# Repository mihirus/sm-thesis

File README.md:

```bash
├── cad
│   ├── cores
│   │   ├── etd44_core.SLDPRT
│   │   ├── etd49_core.SLDPRT
│   │   ├── etd54_core.SLDPRT
│   │   └── etd59_core.SLDPRT
│   ├── etd59_bobbin_integrated_secondary.SLDPRT
│   ├── etd59_shunt_AB.SLDPRT
│   ├── inverter_sink_v2_vertical.SLDPRT
│   └── leakage-transformer-assembly
│       ├── etd59_bobbin_integrated_v7.SLDPRT
│       ├── etd59_core.SLDPRT
│       ├── ETD59-integrated-base-raised-nov21.SLDPRT
│       ├── ETD59-integrated-bottom-raised-0.8mm-dec9.SLDPRT
│       ├── ETD59-integrated-top-raised-0.8mm-dec9.SLDPRT
│       ├── etd59-withsinks-raised-dec9.SLDASM
│       ├── secondary-placeholder.SLDPRT
│       ├── shunt-heat-sink.SLDPRT
│       └── shunt-heat-spreader.SLDPRT
├── optimization
│   ├── opt_baseline.py
│   ├── opt_heatsink.py
│   └── opt_integrated.py
├── pcb
│   ├── custom_assets (collapsed)
│   ├── inverter
│   │   ├── half_bridge.kicad_sch
│   │   ├── inverter.kicad_pcb
│   │   ├── inverter.kicad_prl
│   │   ├── inverter.kicad_pro
│   │   ├── inverter.kicad_sch
│   │   ├── inverter.pdf
│   │   ├── inverter.round-tracks-config
│   │   ├── inverter.step
│   │   └── outputs
│   │       ├── inverter-B_Cu.pdf
│   │       ├── inverter-F_Cu.pdf
│   │       ├── inverter-In1_Cu.pdf
│   │       └── inverter-In2_Cu.pdf
│   ├── multiplier-slu15mg-2p
│   │   ├── full_wave_cell-.kicad_sch
│   │   ├── full_wave_cell.kicad_sch
│   │   ├── multiplier-slu15mg.kicad_pcb
│   │   ├── multiplier-slu15mg.kicad_prl
│   │   ├── multiplier-slu15mg.kicad_pro
│   │   ├── multiplier-slu15mg.kicad_sch
│   │   ├── multiplier-slu15mg.step
│   │   └── outputs
│   │       ├── multiplier-slu15mg-B_Cu.pdf
│   │       ├── multiplier-slu15mg-Edge_Cuts.pdf
│   │       └── multiplier-slu15mg-F_Cu.pdf
│   └── tank-caps
│       ├── tank-caps.kicad_pcb
│       ├── tank-caps.kicad_prl
│       ├── tank-caps.kicad_pro
│       ├── tank-caps.kicad_sch
│       └── tank-caps.step
├── README.md
└── simulation
    ├── electromagnetic
    │   └── horizontal-interleaved-shunt-kenneth-muhammad.aedt
    └── thermal
        ├── etd59_core.aedt
        ├── inverter_heatsink_v2_vertical.aedt
        ├── thermal_horizontal_winding_cross_section_with_air.aedt
        └── thermal_horizontal_winding_cross_section_with_compound.aedt
```

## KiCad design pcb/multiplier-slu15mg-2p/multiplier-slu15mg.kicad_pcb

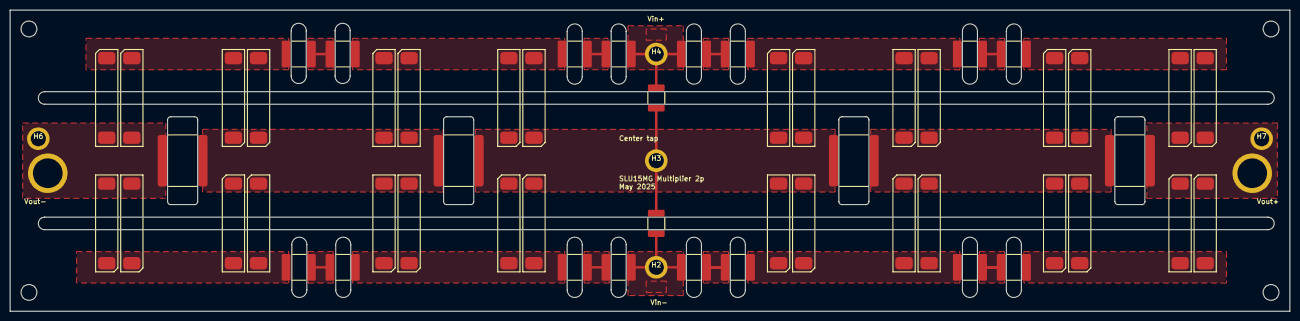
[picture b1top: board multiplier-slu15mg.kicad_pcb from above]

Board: 2 copper layers, 259.1 x 61.0 mm, 61 parts (0 on the bottom side), 23 nets.

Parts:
C1, C2, C3, C4, C6, C7, C8, C9, C11, C12, C13, C14, C16, C17, C18, C19: C; C_2220_5750Metric
C5, C10, C15, C20: C; C_3640_9110Metric_HV
C21, C22: C; C_1812_4532Metric
D1, D2, D3, D4, D5, D6, D7, D8, D9, D10, D11, D12, D13, D14, D15, D16, D17, D18, D19, D20, D21, D22, D23, D24, D25, D26, D27, D28, D29, D30, D31, D32: D; slu15mg
H1, H2, H3, H4, H5: MountingHole_Pad; hv_clip_pth_6mm
H6, H7: MountingHole_Pad; output_pad_4mm

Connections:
/full_wave_cell1/O+: C8.2, C16.1, D5.2 (A), D7.1 (K), D25.1 (K), D29.2 (A)
/full_wave_cell1/O-: C9.2, C17.1, D6.2 (A), D8.1 (K), D26.1 (K), D30.2 (A)
/full_wave_cell1/O=: C10.2, C20.1, D7.2 (A), D8.2 (A), D13.1 (K), D14.1 (K), D25.2 (A), D26.2 (A), D31.1 (K), D32.1 (K)
/full_wave_cell2/O+: C13.2, D9.1 (K), D11.2 (A), D18.1 (K), D24.2 (A)
/full_wave_cell2/O-: C14.2, D10.1 (K), D12.2 (A), D20.1 (K), D22.2 (A)
/full_wave_cell2/O=: C15.2, D11.1 (K), D12.1 (K), D22.1 (K), D24.1 (K), H5.1, H7.1
/full_wave_cell3/O+: C18.2, D13.2 (A), D15.1 (K), D27.1 (K), D31.2 (A)
/full_wave_cell3/O-: C19.2, D14.2 (A), D16.1 (K), D28.1 (K), D32.2 (A)
/full_wave_cell3/O=: C20.2, D15.2 (A), D16.2 (A), D27.2 (A), D28.2 (A), H1.1, H6.1
/full_wave_cell/I+: C1.1, C7.1, C21.2, H4.1
/full_wave_cell/I-: C2.1, C6.1, C22.2, H2.1
/full_wave_cell/I=: C5.1, C10.1, C21.1, C22.1, D1.2 (A), D2.2 (A), D5.1 (K), D6.1 (K), D17.2 (A), D19.2 (A), D29.1 (K), D30.1 (K), H3.1
/full_wave_cell/O+: C3.2, C11.1, D1.1 (K), D3.2 (A), D17.1 (K), D23.2 (A)
/full_wave_cell/O-: C4.2, C12.1, D2.1 (K), D4.2 (A), D19.1 (K), D21.2 (A)
/full_wave_cell/O=: C5.2, C15.1, D3.1 (K), D4.1 (K), D9.2 (A), D10.2 (A), D18.2 (A), D20.2 (A), D21.1 (K), D23.1 (K)
unnamed: C1.2, C3.1
unnamed: C2.2, C4.1
unnamed: C6.2, C8.1
unnamed: C7.2, C9.1
unnamed: C11.2, C13.1
unnamed: C12.2, C14.1
unnamed: C16.2, C18.1
unnamed: C17.2, C19.1

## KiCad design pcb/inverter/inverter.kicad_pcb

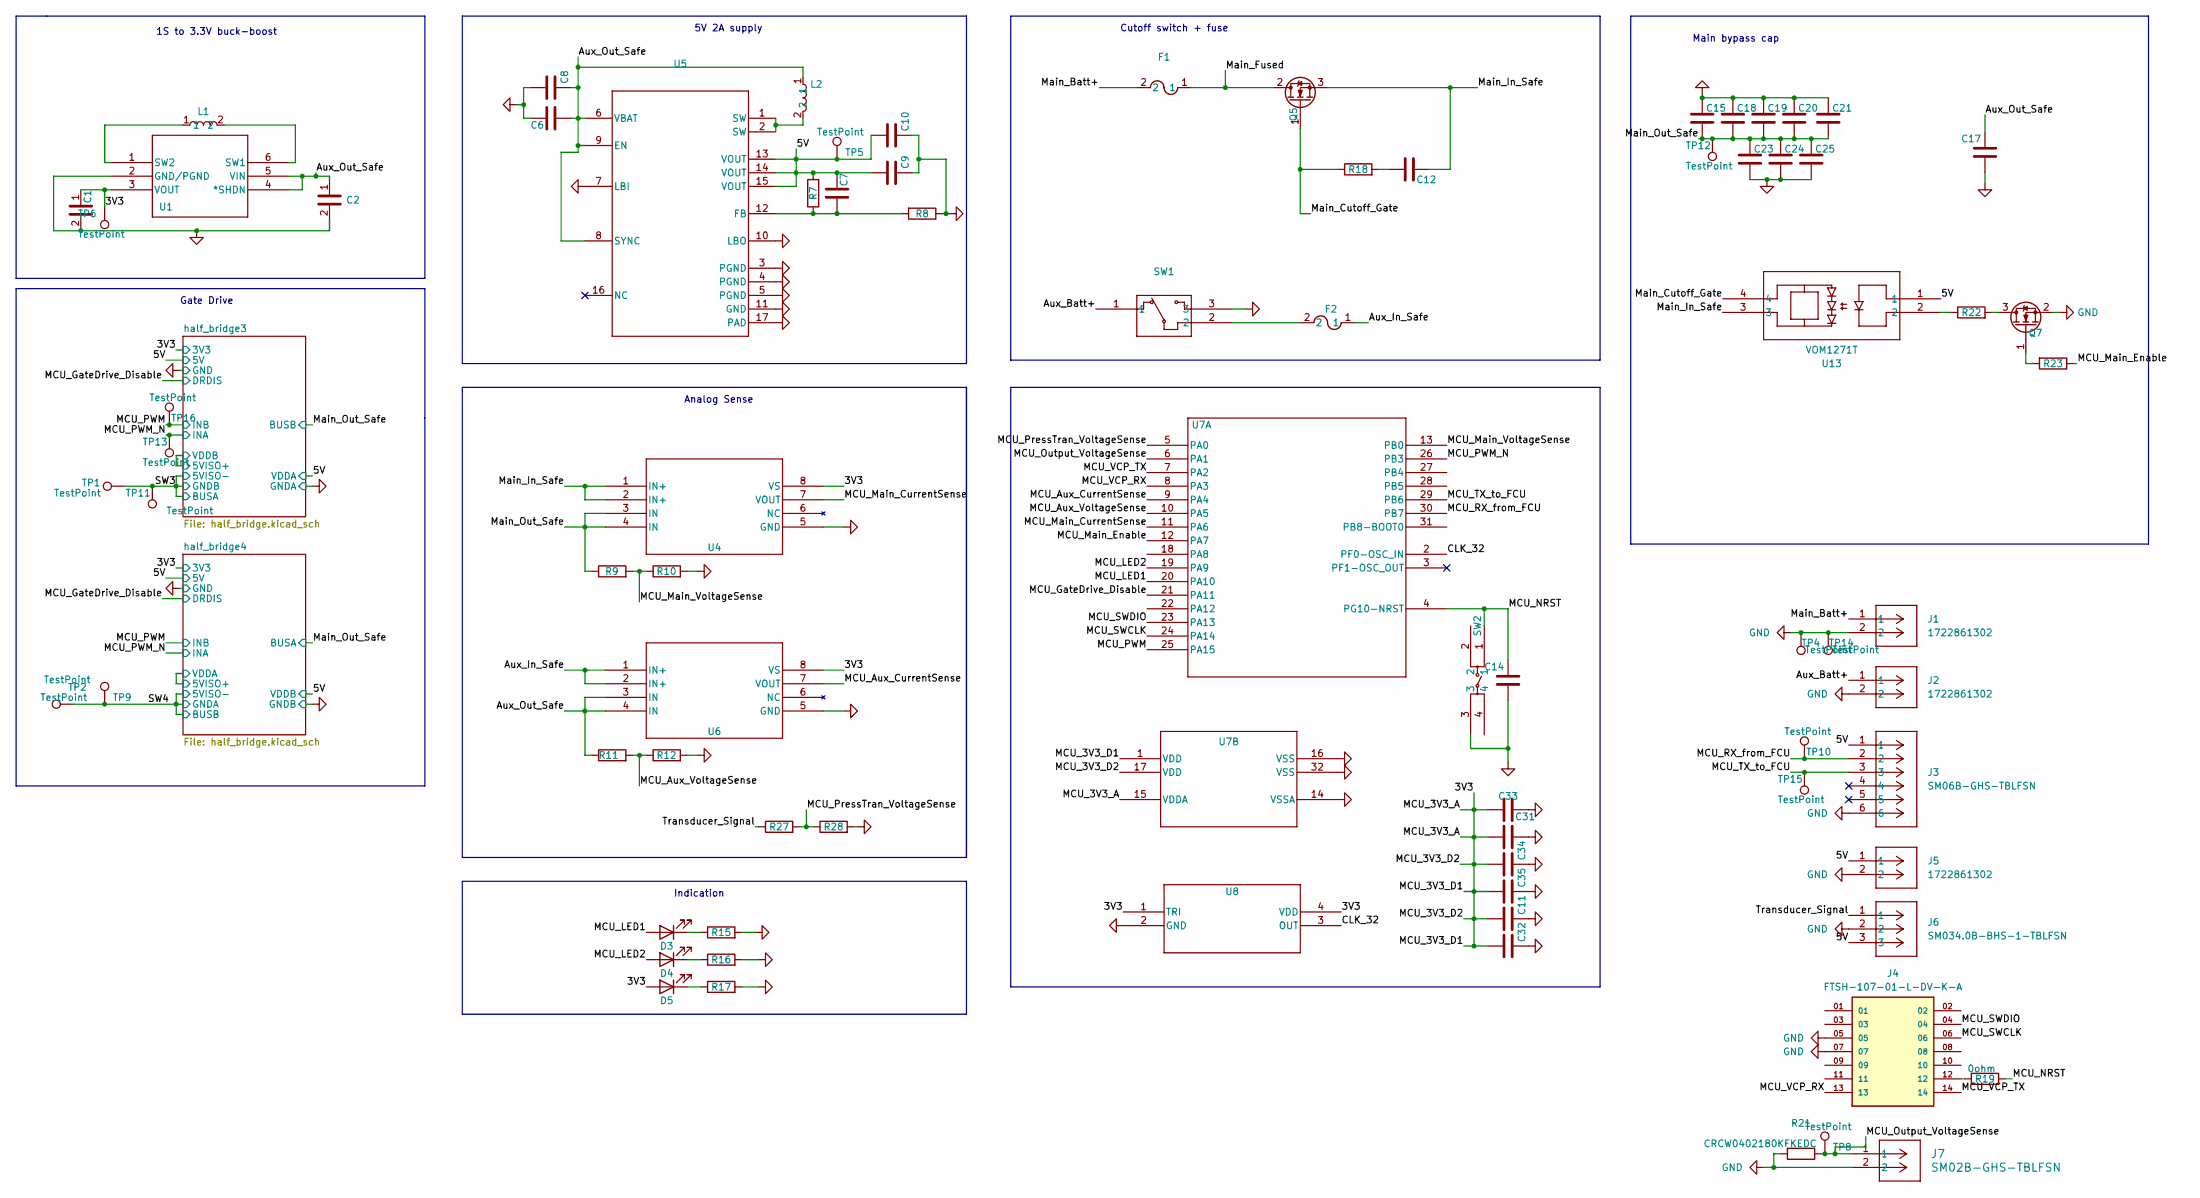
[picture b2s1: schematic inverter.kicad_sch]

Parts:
C1: GRT21BR61C226ME13K; C_0805_2012Metric
C2: CL21B475KOQVPNE; C_0805_2012Metric
C6: CGA5L3X5R1H106M160AB; C_1206_3216Metric
C7: KGQ05FCG1H100FH; C_0603_1608Metric
C8, C11, C14, C32: C1005X7R1H104K050BB; C_0603_1608Metric
C9: CKG57NX7R1V107M500JJ; C_2220_5650Metric_Pad1.97x5.40mm_HandSolder
C10: C2012X7R1H225K125AC; C_0805_2012Metric
C12: C; C_0603_1608Metric
C15, C18, C19, C20, C21, C23, C24, C25: 2220Y5000105KJTWS2; C_2220_5650Metric
C17: C3216X7R1E106K160AB; C_1206_3216Metric
C31: C1608X7R1V105K080AE; C_0603_1608Metric
C33: C1005X7R1H103K050BB; C_0603_1608Metric
C34, C35: GRM188Z71A475KE15J; C_0603_1608Metric
D3: QBLP601-R5; LED_0603_1608Metric
D4: QBLP601-AG15; LED_0603_1608Metric
D5: QBLP601-IB5; LED_0603_1608Metric
F1: TR-1350HV5-R; FUSE_1350HV_EAT
F2: TR-1350HV2-R; FUSE_1350HV_EAT
J1, J2, J5: 1722861302; CON_1722861302_MOL
J3: SM06B-GHS-TBLFSN; CONN_SM06B-GHS-TB_JST
J4: FTSH-107-01-L-DV-K-A; SAMTEC_FTSH-107-01-L-DV-K-A; PARTREV H; DigiKey_Part_Number FTSH-107-01-L-DV-K-A-ND
J6: SM034.0B-BHS-1-TBLFSN; CONN_SM034.0B-BHS-1-TB_JST
J7: SM02B-GHS-TBLFSN; CONN_SM02B-GHS-TBLFSN_JST
L1: LSXND3030QKT100MNG
L2: 74438357022; L_Wuerth_MAPI-4020
Q5: UF3C065030T3S; TO-220-3_Vertical
Q7: SSM3K35AFS; SOT-416
R7: RMCF0603FT1M62; R_0603_1608Metric
R8: CRCW0603180KFKEAHP; R_0603_1608Metric
R9: TNPV08051M00BEEA; R_0805_2012Metric
R10, R11, R12: MCT0603MD1002BP500; R_0603_1608Metric
R15: RK73H1JTTD3000F; R_0603_1608Metric
R16: RK73H1JTTD2800F; R_0603_1608Metric
R17: RK73H1JTTD82R0F; R_0603_1608Metric
R18: R; R_0603_1608Metric
R19: 0ohm; R_0603_1608Metric
R21: CRCW0402180KFKEDC; R_0603_1608Metric
R22: RK73H1ETTP3600F; R_0603_1608Metric
R23: RK73H1ETTP1001F; R_0603_1608Metric
R27: RK73H1ETTP2203F; R_0603_1608Metric
R28: RMCF0603FT280K; R_0603_1608Metric
SW1: 500ASSP3M2QE; 500ASSP3M2QE_EWI
SW2: PTS 647 SN50 SMTR2 LFS
TP1, TP2: TestPoint; output_pad_4x8mm
TP4, TP14: TestPoint; TestPoint_Keystone_5010-5014_Multipurpose
TP5, TP6, TP8, TP9, TP10, TP11, TP12, TP13, TP15, TP16: TestPoint; TestPoint_Keystone_5000-5004_Miniature
U1: LTC3531; TSOT-23-6
U4, U6: TMCS1101A3UQDT; TMCS1101
U5: TPS61030PWP; PWP0016K_L
U7: STM32G431KBT6; LQFP-32
U8: ECS-TXO-2520MV-320-AN-TR; SMD04_XTAL_2P5X2_ECS
U13: VOM1271T; SOP-4_VIS-L

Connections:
/3V3: C1.1, C11.1, C31.1, C32.1, C33.1, C34.1, C35.1, D5.2 (A), TP6.1, U1.3 (VOUT), U4.8 (VS), U6.8 (VS), U7.1 (VDD), U7.15 (VDDA), U7.17 (VDD), U8.1 (TRI), U8.4 (VDD); also elsewhere on the board
/5V: C7.2, C9.1, C10.1, J3.1, J5.1, J6.3, R7.2, TP5.1, U5.13 (VOUT), U5.14 (VOUT), U5.15 (VOUT), U13.1; also elsewhere on the board
/Aux_Batt+: J2.1, SW1.1
/Aux_In_Safe: F2.1, U6.1 (IN+), U6.2 (IN+)
/Aux_Out_Safe: C2.1, C6.2, C8.2, C17.2, L2.1, R11.1, U1.4 (*SHDN), U1.5 (VIN), U5.6 (VBAT), U5.8 (SYNC), U5.9 (EN), U6.3 (IN), U6.4 (IN)
/CLK_32: U7.2 (PF0-OSC_IN), U8.3 (OUT)
/MCU_Aux_CurrentSense: U6.7 (VOUT), U7.9 (PA4)
/MCU_Aux_VoltageSense: R11.2, R12.1, U7.10 (PA5)
/MCU_GateDrive_Disable: U7.21 (PA11); also elsewhere on the board
/MCU_LED1: D3.2 (A), U7.20 (PA10)
/MCU_LED2: D4.2 (A), U7.19 (PA9)
/MCU_Main_CurrentSense: U4.7 (VOUT), U7.11 (PA6)
/MCU_Main_Enable: R23.1, U7.12 (PA7)
/MCU_Main_VoltageSense: R9.2, R10.1, U7.13 (PB0)
/MCU_NRST: C14.2, R19.2, SW2.1, U7.4 (PG10-NRST)
/MCU_Output_VoltageSense: J7.1, R21.1, TP8.1, U7.6 (PA1)
/MCU_PWM: TP16.1, U7.25 (PA15); also elsewhere on the board
/MCU_PWM_N: TP13.1, U7.26 (PB3); also elsewhere on the board
/MCU_PressTran_VoltageSense: R27.2, R28.1, U7.5 (PA0)
/MCU_RX_from_FCU: J3.2, TP10.1, U7.30 (PB7)
/MCU_SWCLK: J4.06, U7.24 (PA14)
/MCU_SWDIO: J4.04, U7.23 (PA13)
/MCU_TX_to_FCU: J3.3, TP15.1, U7.29 (PB6)
/MCU_VCP_RX: J4.13, U7.8 (PA3)
/MCU_VCP_TX: J4.14, U7.7 (PA2)
/Main_Batt+: F1.2, J1.1
/Main_Cutoff_Gate: Q5.1 (G), R18.1, U13.4
/Main_Fused: F1.1, Q5.2 (D)
/Main_In_Safe: C12.2, Q5.3 (S), U4.1 (IN+), U4.2 (IN+), U13.3
/Main_Out_Safe: C15.2, C18.2, C19.2, C20.2, C21.2, C23.1, C24.1, C25.1, R9.1, TP12.1, U4.3 (IN), U4.4 (IN); also elsewhere on the board
/SW3: TP1.1, TP11.1; also elsewhere on the board
/SW4: TP2.1, TP9.1; also elsewhere on the board
/Transducer_Signal: J6.1, R27.1
GND: C1.2, C2.2, C6.1, C8.1, C9.2, C10.2, C11.2, C14.1, C15.1, C17.1, C18.1, C19.1, C20.1, C21.1, C23.2, C24.2, C25.2, C31.2, C32.2, C33.2, C34.2, C35.2, J1.2, J2.2, J3.6, J4.05, J4.07, J5.2, J6.2, J7.2, Q7.2 (S), R8.1, R10.2, R12.2, R15.2, R16.2, R17.2, R21.2, R28.2, SW1.3, SW2.3, TP4.1, TP14.1, U1.2 (GND/PGND), U4.5 (GND), U5.3 (PGND), U5.4 (PGND), U5.5 (PGND), U5.7 (LBI), U5.10 (LBO), U5.11 (GND), U5.17 (PAD), U6.5 (GND), U7.14 (VSSA), U7.16 (VSS), U7.32 (VSS), U8.2 (GND); also elsewhere on the board
unnamed: C12.1, R18.2
unnamed: D3.1 (K), R15.1
unnamed: D4.1 (K), R16.1
unnamed: D5.1 (K), R17.1
unnamed: F2.2, SW1.2
unnamed: J4.12, R19.1
unnamed: L2.2, U5.1 (SW), U5.2 (SW)
unnamed: Q7.3 (D), R22.2
unnamed: Q7.1 (G), R23.2
unnamed: R22.1, U13.2
unnamed: L1.2, U1.6 (SW1)
unnamed: L1.1, U1.1 (SW2)
unnamed: C7.1, R7.1, R8.2, U5.12 (FB)

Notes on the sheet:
5V 2A supply
Indication
1S to 3.3V buck-boost
Gate Drive
Cutoff switch + fuse
Analog Sense
Main bypass cap

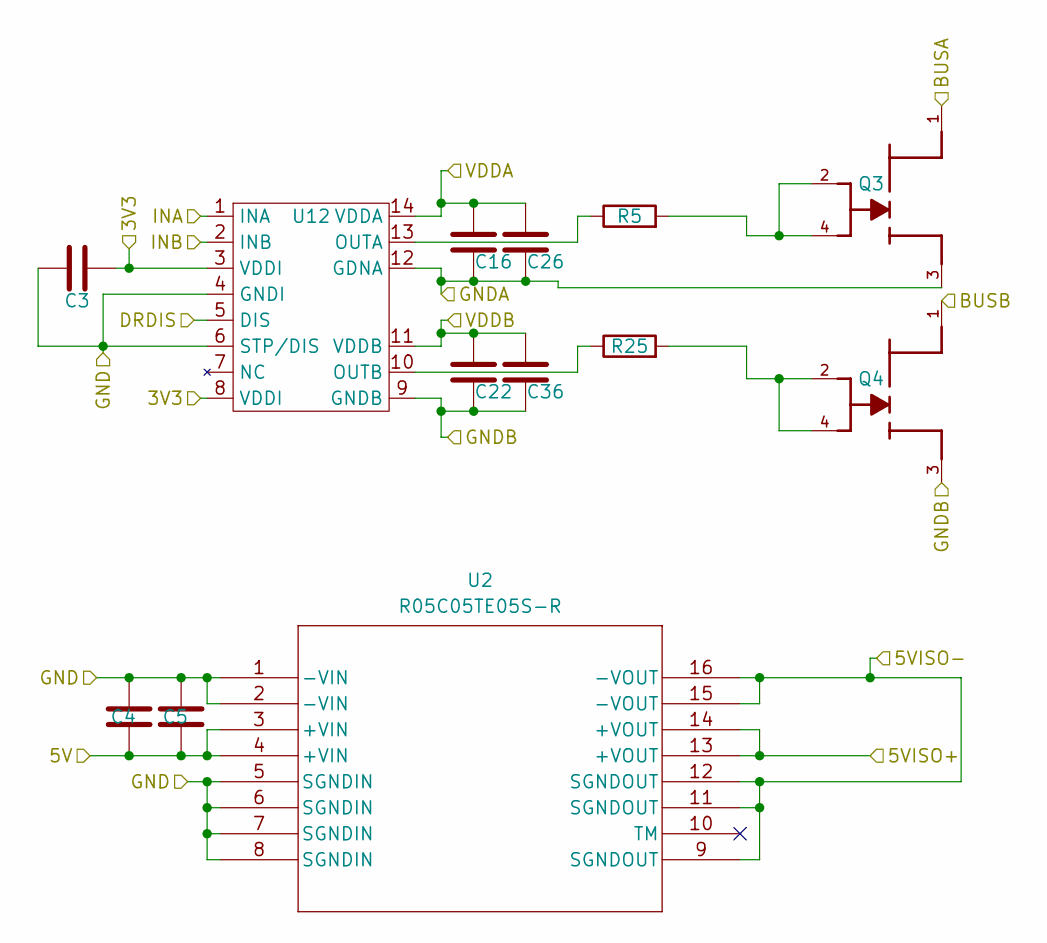
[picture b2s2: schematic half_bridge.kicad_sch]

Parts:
C3, C5: CGA3E1X7R1E105K080AC; C_0603_1608Metric
C4: CL21B106KOQNNNG; C_0805_2012Metric
C16, C22: C0805X473J3GECAUTO; C_0805_2012Metric
C26, C36: GRM31C5C1E474JE01L; C_1206_3216Metric
Q3, Q4: GS66516T-MR; TRANS_GS66516T-MR; PARTREV Rev 210727
R5, R25: CRCW06034R70FKEAHP; R_0603_1608Metric
U2: R05C05TE05S-R; SMD_16_10.35X7.5X2.5_RCP
U12: 2EDR7259X

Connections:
/3V3: C3.2, U12.3 (VDDI), U12.8 (VDDI); also elsewhere on the board
/5V: C4.2, C5.2, C22.1, C36.1, U2.3 (+VIN), U2.4 (+VIN), U12.11 (VDDB); also elsewhere on the board
/MCU_GateDrive_Disable: U12.5 (DIS); also elsewhere on the board
/MCU_PWM: U12.2 (INB); also elsewhere on the board
/MCU_PWM_N: U12.1 (INA); also elsewhere on the board
/Main_Out_Safe: Q3.1; also elsewhere on the board
/SW4: C16.2, C26.2, Q3.3, Q4.1, U2.9 (SGNDOUT), U2.11 (SGNDOUT), U2.12 (SGNDOUT), U2.15 (-VOUT), U2.16 (-VOUT), U12.12 (GDNA); also elsewhere on the board
/half_bridge4/5VISO+: C16.1, C26.1, U2.13 (+VOUT), U2.14 (+VOUT), U12.14 (VDDA)
GND: C3.1, C4.1, C5.1, C22.2, C36.2, Q4.3, U2.1 (-VIN), U2.2 (-VIN), U2.5 (SGNDIN), U2.6 (SGNDIN), U2.7 (SGNDIN), U2.8 (SGNDIN), U12.4 (GNDI), U12.6 (STP/DIS), U12.9 (GNDB); also elsewhere on the board
unnamed: Q3.2, Q3.4, R5.2
unnamed: Q4.2, Q4.4, R25.2
unnamed: R5.1, U12.13 (OUTA)
unnamed: R25.1, U12.10 (OUTB)

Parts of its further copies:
C27, C29: CGA3E1X7R1E105K080AC; C_0603_1608Metric
C28: CL21B106KOQNNNG; C_0805_2012Metric
C30, C40: C0805X473J3GECAUTO; C_0805_2012Metric
C43, C44: GRM31C5C1E474JE01L; C_1206_3216Metric
Q1, Q2: GS66516T-MR; TRANS_GS66516T-MR; PARTREV Rev 210727
R1, R3: CRCW06034R70FKEAHP; R_0603_1608Metric
U3: R05C05TE05S-R; SMD_16_10.35X7.5X2.5_RCP
U11: 2EDR7259X

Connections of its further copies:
/3V3: C27.2, U11.3 (VDDI), U11.8 (VDDI); also elsewhere on the board
/5V: C28.2, C29.2, C30.1, C43.1, U3.3 (+VIN), U3.4 (+VIN), U11.14 (VDDA); also elsewhere on the board
/MCU_GateDrive_Disable: U11.5 (DIS); also elsewhere on the board
/MCU_PWM: U11.2 (INB); also elsewhere on the board
/MCU_PWM_N: U11.1 (INA); also elsewhere on the board
/Main_Out_Safe: Q1.1; also elsewhere on the board
/SW3: C40.2, C44.2, Q1.3, Q2.1, U3.9 (SGNDOUT), U3.11 (SGNDOUT), U3.12 (SGNDOUT), U3.15 (-VOUT), U3.16 (-VOUT), U11.9 (GNDB); also elsewhere on the board
/half_bridge3/5VISO+: C40.1, C44.1, U3.13 (+VOUT), U3.14 (+VOUT), U11.11 (VDDB)
GND: C27.1, C28.1, C29.1, C30.2, C43.2, Q2.3, U3.1 (-VIN), U3.2 (-VIN), U3.5 (SGNDIN), U3.6 (SGNDIN), U3.7 (SGNDIN), U3.8 (SGNDIN), U11.4 (GNDI), U11.6 (STP/DIS), U11.12 (GDNA); also elsewhere on the board
unnamed: Q1.2, Q1.4, R3.2
unnamed: Q2.2, Q2.4, R1.2
unnamed: R1.1, U11.13 (OUTA)
unnamed: R3.1, U11.10 (OUTB)

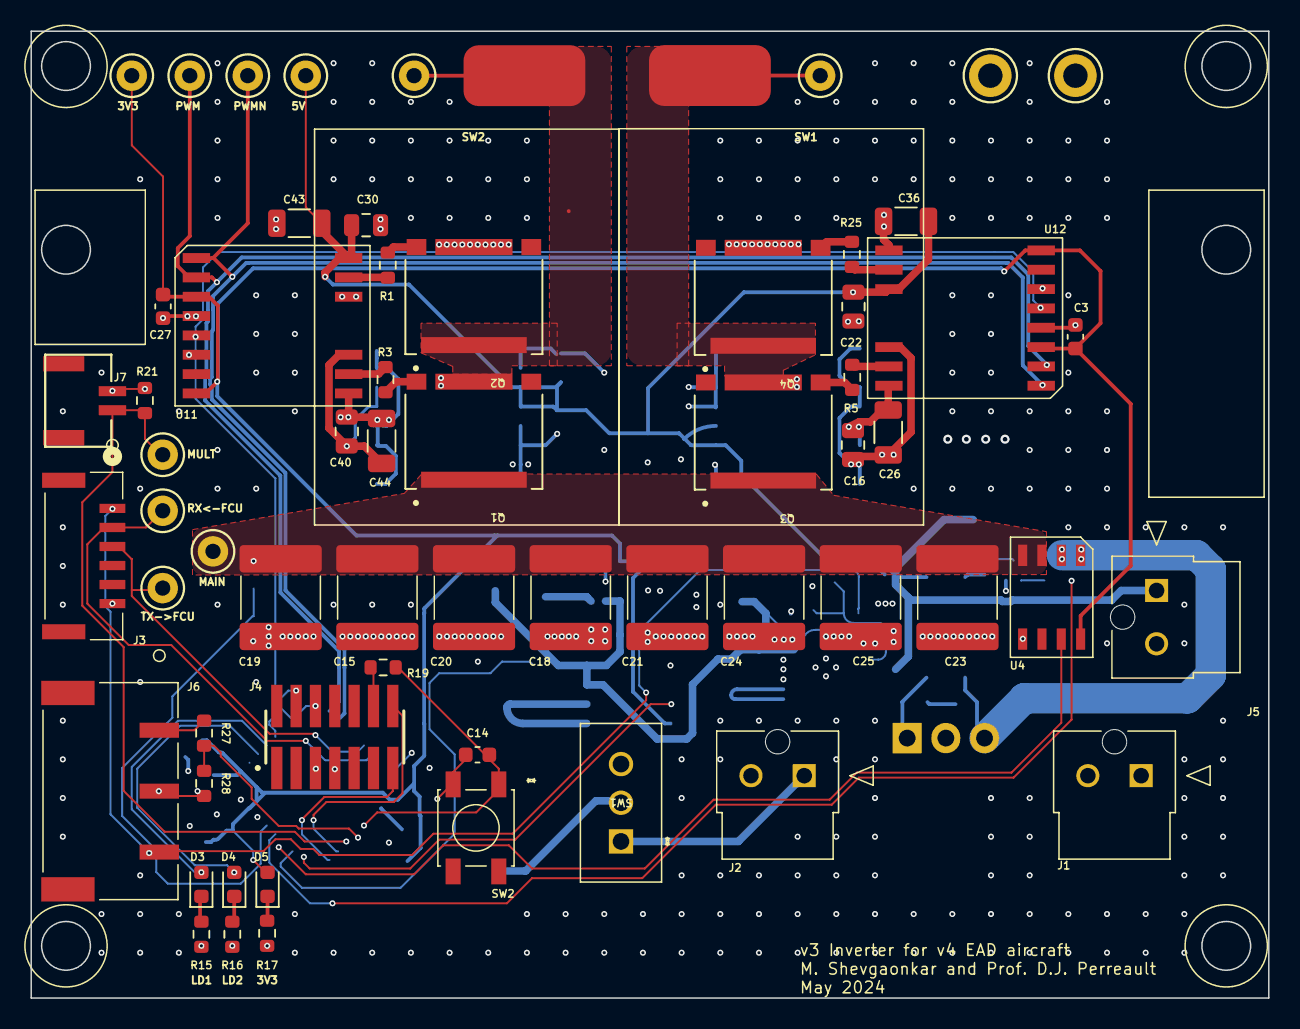
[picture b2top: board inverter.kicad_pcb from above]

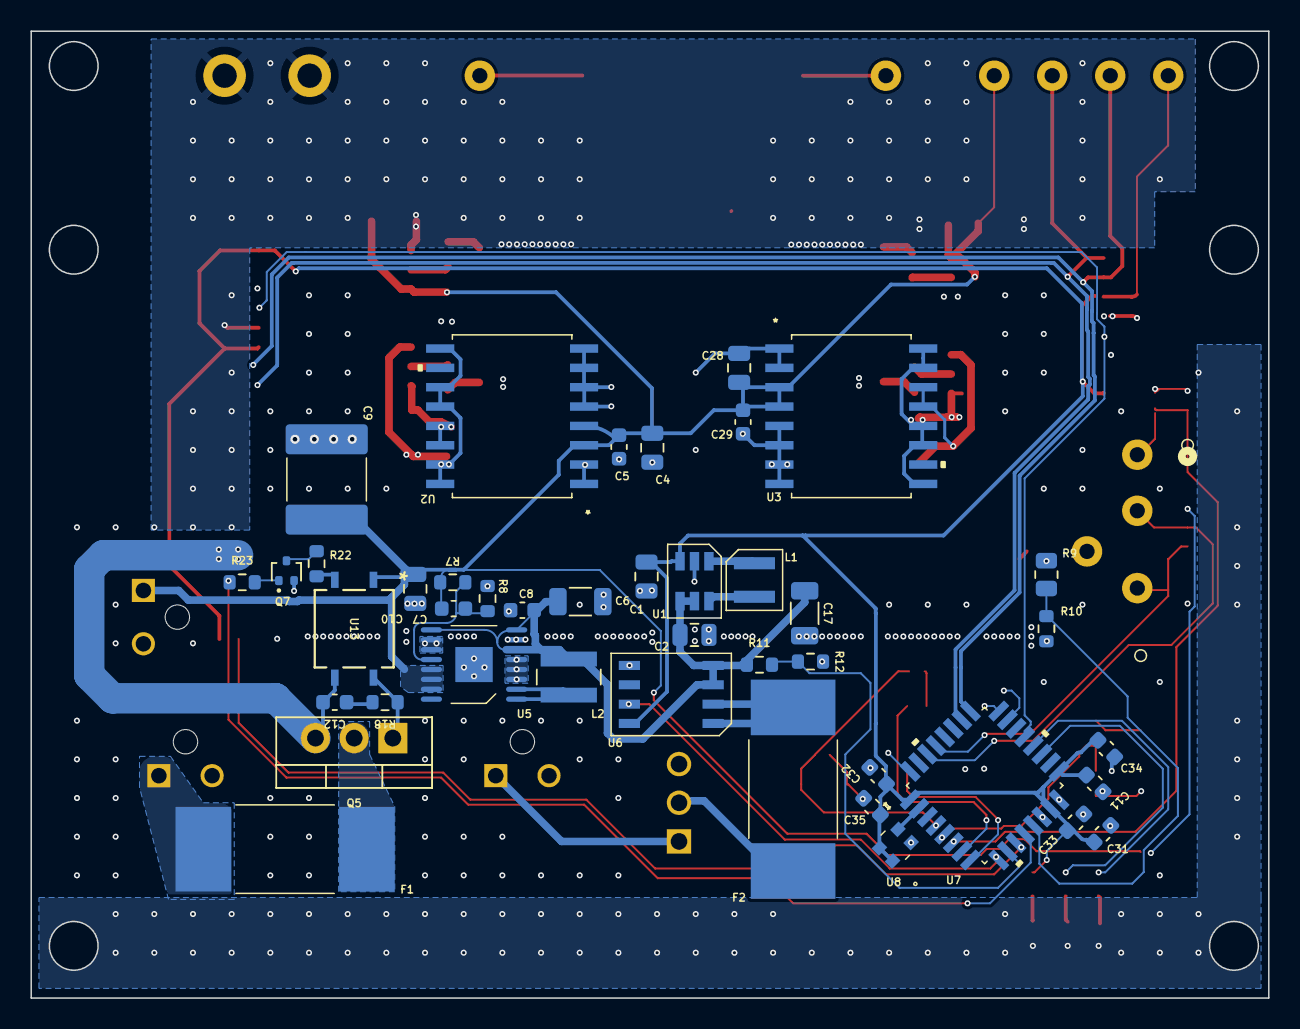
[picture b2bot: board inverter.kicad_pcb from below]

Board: 4 copper layers, 81.3 x 63.5 mm, 105 parts (42 on the bottom side), 57 nets.

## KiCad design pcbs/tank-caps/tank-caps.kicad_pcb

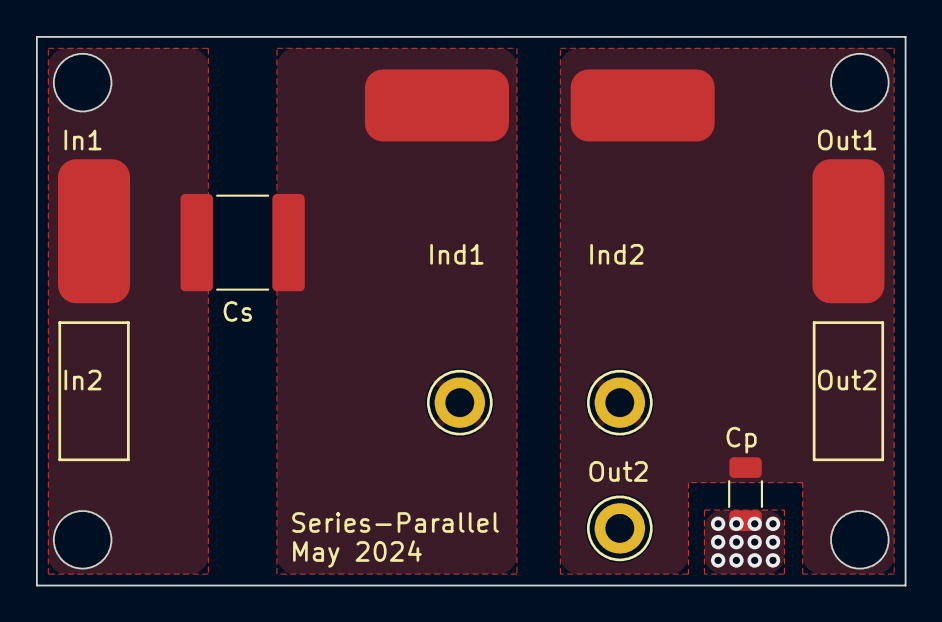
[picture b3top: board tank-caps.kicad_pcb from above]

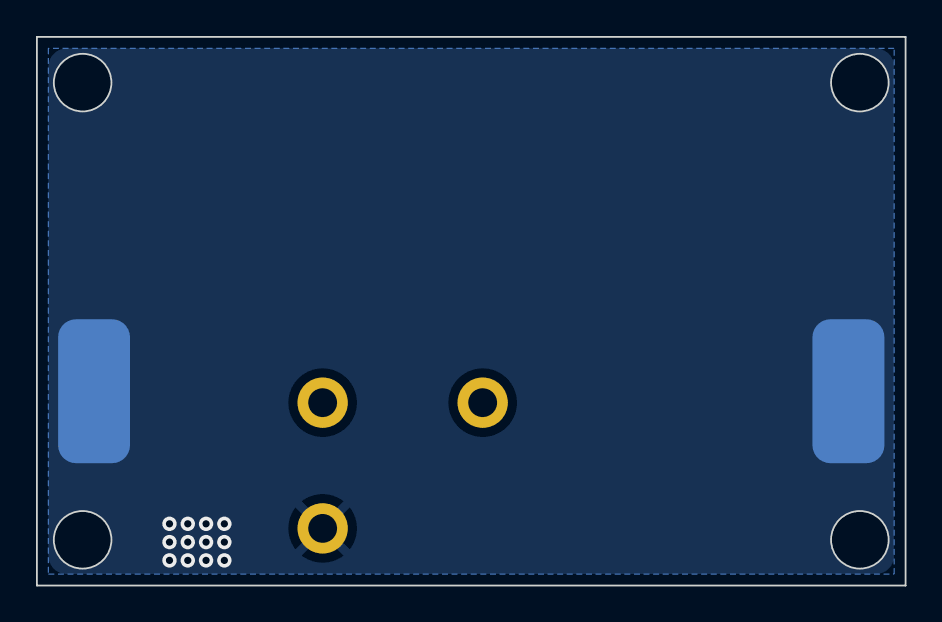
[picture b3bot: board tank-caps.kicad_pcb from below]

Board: 2 copper layers, 48.3 x 30.5 mm, 11 parts (2 on the bottom side), 4 nets, no tracks yet.

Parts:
C1: Cp; C_1206_3216Metric
C2: Cs; C_2220_5750Metric
TP1, TP2, TP3, TP4, TP5, TP6: TestPoint; output_pad_4x8mm
TP7, TP8, TP9: TestPoint; TestPoint_Keystone_5005-5009_Compact

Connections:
unnamed: C1.1, TP4.1, TP5.1, TP8.1
unnamed: C1.2, TP2.1, TP6.1, TP7.1
unnamed: C2.1, TP1.1
unnamed: C2.2, TP3.1, TP9.1

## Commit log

2025-12-01 add optimization routines, pcbs, readme
2025-12-01 add simulation and cad files
